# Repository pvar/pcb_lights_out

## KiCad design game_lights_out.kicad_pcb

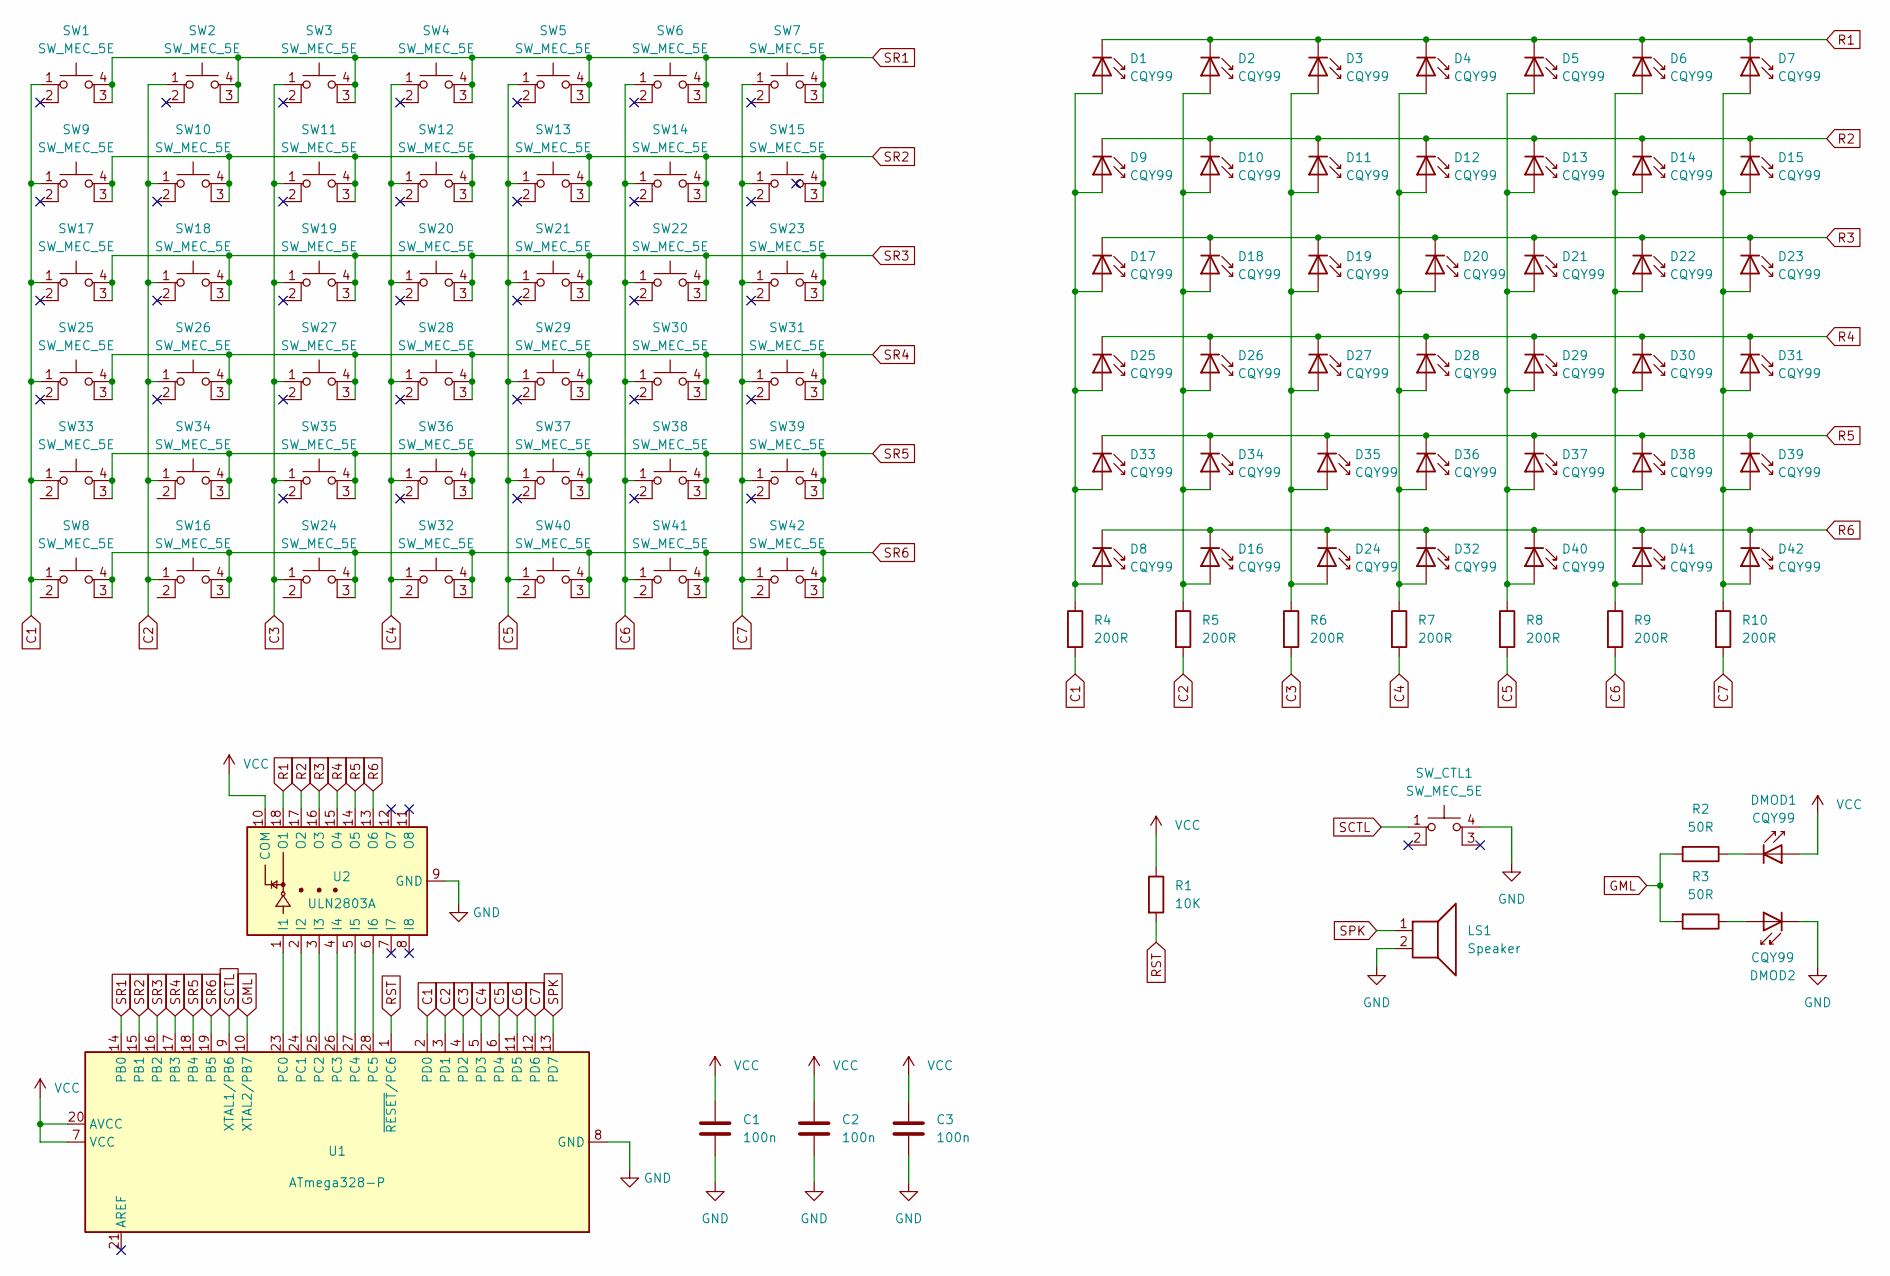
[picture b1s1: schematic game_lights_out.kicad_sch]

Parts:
C1, C2, C3: 100n; C_Rect_L4.6mm_W2.0mm_P2.50mm_MKS02_FKP02
D1, D2, D3, D4, D5, D6, D7, D8, D9, D10, D11, D12, D13, D14, D15, D16, D17, D18, D19, D20, D21, D22, D23, D24, D25, D26, D27, D28, D29, D30, D31, D32, D33, D34, D35, D36, D37, D38, D39, D40, D41, D42: CQY99; LED_D5.0mm
DMOD1, DMOD2: CQY99; LED_D1.8mm_W3.3mm_H2.4mm
LS1: Speaker; PinHeader_1x02_P2.54mm_Vertical
R1: 10K; R_Axial_DIN0207_L6.3mm_D2.5mm_P7.62mm_Horizontal
R2, R3: 50R; R_Axial_DIN0207_L6.3mm_D2.5mm_P7.62mm_Horizontal
R4, R5, R6, R7, R8, R9, R10: 200R; R_Axial_DIN0207_L6.3mm_D2.5mm_P7.62mm_Horizontal
SW1, SW2, SW3, SW4, SW5, SW6, SW7, SW8, SW9, SW10, SW11, SW12, SW13, SW14, SW15, SW16, SW17, SW18, SW19, SW20, SW21, SW22, SW23, SW24, SW25, SW26, SW27, SW28, SW29, SW30, SW31, SW32, SW33, SW34, SW35, SW36, SW37, SW38, SW39, SW40, SW41, SW42: SW_MEC_5E; SW_PUSH_6mm_H5mm
SW_CTL1: SW_MEC_5E; SW_PUSH_6mm_H5mm
U1: ATmega328-P; DIP-28_W7.62mm
U2: ULN2803A; DIP-18_W7.62mm

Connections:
C1: R4.2, SW1.1, SW8.1, SW9.1, SW17.1, SW25.1, SW33.1, U1.2 (PD0)
C2: R5.2, SW2.1, SW10.1, SW16.1, SW18.1, SW26.1, SW34.1, U1.3 (PD1)
C3: R6.2, SW3.1, SW11.1, SW19.1, SW24.1, SW27.1, SW35.1, U1.4 (PD2)
C4: R7.2, SW4.1, SW12.1, SW20.1, SW28.1, SW32.1, SW36.1, U1.5 (PD3)
C5: R8.2, SW5.1, SW13.1, SW21.1, SW29.1, SW37.1, SW40.1, U1.6 (PD4)
C6: R9.2, SW6.1, SW14.1, SW22.1, SW30.1, SW38.1, SW41.1, U1.11 (PD5)
C7: R10.2, SW7.1, SW15.1, SW23.1, SW31.1, SW39.1, SW42.1, U1.12 (PD6)
GML: R2.2, R3.2, U1.10 (XTAL2/PB7)
GND: C1.2, C2.2, C3.2, DMOD2.1 (K), LS1.2, SW_CTL1.4 (A), U1.8 (GND), U1.22 (GND), U2.9 (GND)
unnamed: D1.2 (A), D8.2 (A), D9.2 (A), D17.2 (A), D25.2 (A), D33.2 (A), R4.1
unnamed: D2.2 (A), D10.2 (A), D16.2 (A), D18.2 (A), D26.2 (A), D34.2 (A), R5.1
unnamed: D3.2 (A), D11.2 (A), D19.2 (A), D24.2 (A), D27.2 (A), D35.2 (A), R6.1
unnamed: D4.2 (A), D12.2 (A), D20.2 (A), D28.2 (A), D32.2 (A), D36.2 (A), R7.1
unnamed: D5.2 (A), D13.2 (A), D21.2 (A), D29.2 (A), D37.2 (A), D40.2 (A), R8.1
unnamed: D6.2 (A), D14.2 (A), D22.2 (A), D30.2 (A), D38.2 (A), D41.2 (A), R9.1
unnamed: D7.2 (A), D15.2 (A), D23.2 (A), D31.2 (A), D39.2 (A), D42.2 (A), R10.1
unnamed: DMOD1.1 (K), R2.1
unnamed: DMOD2.2 (A), R3.1
unnamed: U1.23 (PC0), U2.1 (I1)
unnamed: U1.24 (PC1), U2.2 (I2)
unnamed: U1.25 (PC2), U2.3 (I3)
unnamed: U1.26 (PC3), U2.4 (I4)
unnamed: U1.27 (PC4), U2.5 (I5)
unnamed: U1.28 (PC5), U2.6 (I6)
R1: D1.1 (K), D2.1 (K), D3.1 (K), D4.1 (K), D5.1 (K), D6.1 (K), D7.1 (K), U2.18 (O1)
R2: D9.1 (K), D10.1 (K), D11.1 (K), D12.1 (K), D13.1 (K), D14.1 (K), D15.1 (K), U2.17 (O2)
R3: D17.1 (K), D18.1 (K), D19.1 (K), D20.1 (K), D21.1 (K), D22.1 (K), D23.1 (K), U2.16 (O3)
R4: D25.1 (K), D26.1 (K), D27.1 (K), D28.1 (K), D29.1 (K), D30.1 (K), D31.1 (K), U2.15 (O4)
R5: D33.1 (K), D34.1 (K), D35.1 (K), D36.1 (K), D37.1 (K), D38.1 (K), D39.1 (K), U2.14 (O5)
R6: D8.1 (K), D16.1 (K), D24.1 (K), D32.1 (K), D40.1 (K), D41.1 (K), D42.1 (K), U2.13 (O6)
RST: R1.2, U1.1 (~RESET/PC6)
SCTL: SW_CTL1.1, U1.9 (XTAL1/PB6)
SPK: LS1.1, U1.13 (PD7)
SR1: SW1.3 (K), SW1.4 (A), SW2.3 (K), SW2.4 (A), SW3.3 (K), SW3.4 (A), SW4.3 (K), SW4.4 (A), SW5.3 (K), SW5.4 (A), SW6.3 (K), SW6.4 (A), SW7.3 (K), SW7.4 (A), U1.14 (PB0)
SR2: SW9.3 (K), SW9.4 (A), SW10.3 (K), SW10.4 (A), SW11.3 (K), SW11.4 (A), SW12.3 (K), SW12.4 (A), SW13.3 (K), SW13.4 (A), SW14.3 (K), SW14.4 (A), SW15.3 (K), SW15.4 (A), U1.15 (PB1)
SR3: SW17.3 (K), SW17.4 (A), SW18.3 (K), SW18.4 (A), SW19.3 (K), SW19.4 (A), SW20.3 (K), SW20.4 (A), SW21.3 (K), SW21.4 (A), SW22.3 (K), SW22.4 (A), SW23.3 (K), SW23.4 (A), U1.16 (PB2)
SR4: SW25.3 (K), SW25.4 (A), SW26.3 (K), SW26.4 (A), SW27.3 (K), SW27.4 (A), SW28.3 (K), SW28.4 (A), SW29.3 (K), SW29.4 (A), SW30.3 (K), SW30.4 (A), SW31.3 (K), SW31.4 (A), U1.17 (PB3)
SR5: SW33.3 (K), SW33.4 (A), SW34.3 (K), SW34.4 (A), SW35.3 (K), SW35.4 (A), SW36.3 (K), SW36.4 (A), SW37.3 (K), SW37.4 (A), SW38.3 (K), SW38.4 (A), SW39.3 (K), SW39.4 (A), U1.18 (PB4)
SR6: SW8.3 (K), SW8.4 (A), SW16.3 (K), SW16.4 (A), SW24.3 (K), SW24.4 (A), SW32.3 (K), SW32.4 (A), SW40.3 (K), SW40.4 (A), SW41.3 (K), SW41.4 (A), SW42.3 (K), SW42.4 (A), U1.19 (PB5)
VCC: C1.1, C2.1, C3.1, DMOD1.2 (A), R1.1, U1.7 (VCC), U1.20 (AVCC), U2.10 (COM)

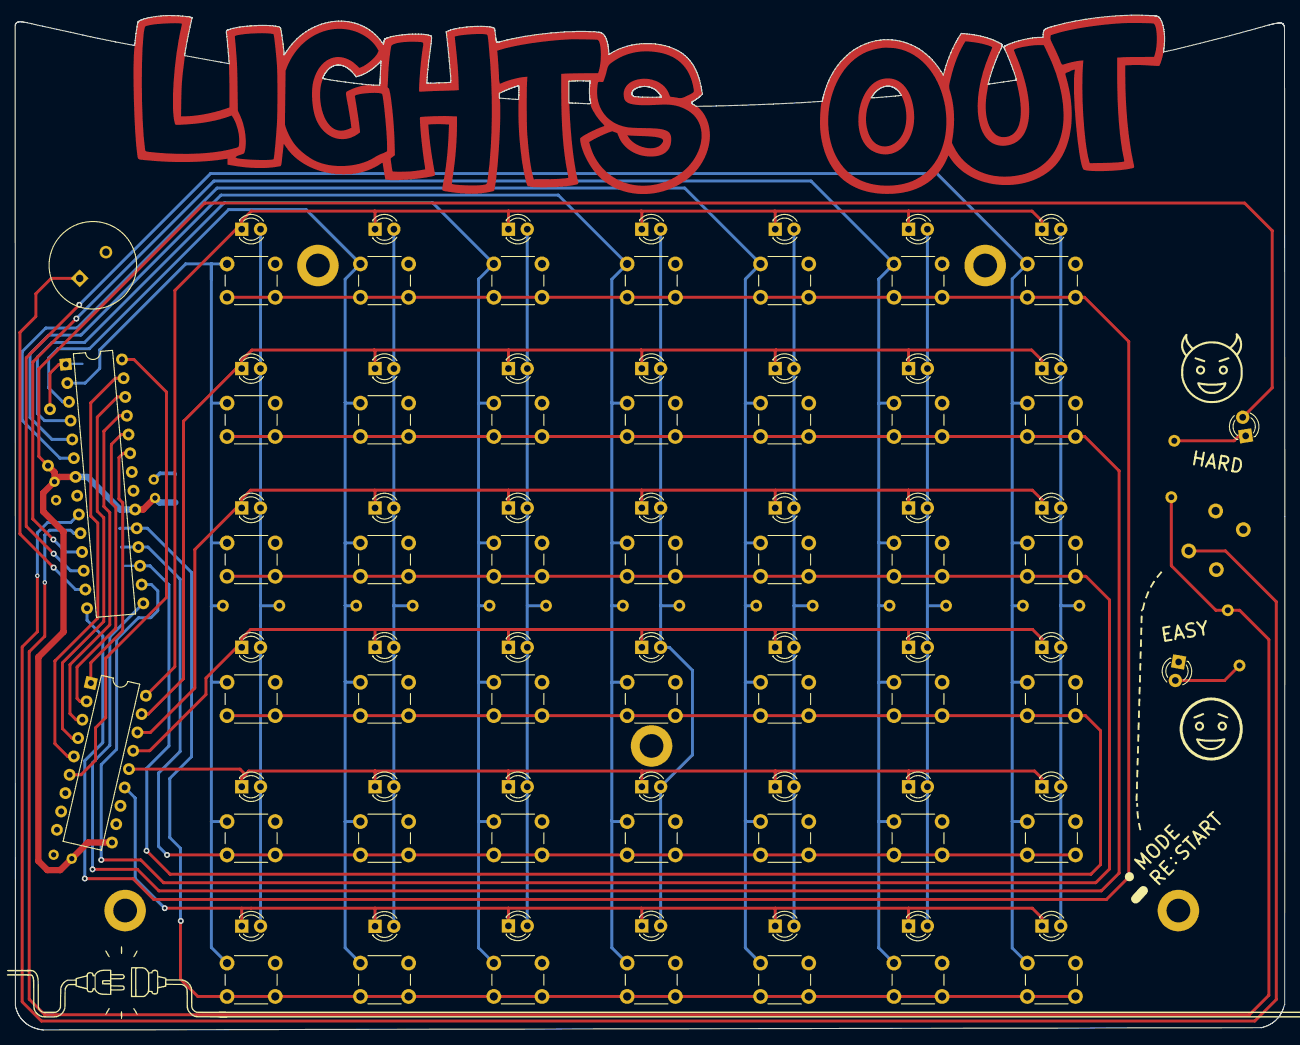
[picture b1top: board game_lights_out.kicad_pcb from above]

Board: 2 copper layers, 171.2 x 136.9 mm, 103 parts (0 on the bottom side), 40 nets.

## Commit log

2023-08-28 Final iteration
2023-08-28 Add signature on back silkscreen
2023-08-29 Added labels to programming pins and updated file format
2023-08-29 Removed reset pin resistor
2023-08-29 Added mounting holes
2023-08-29 Improved switch traces
2023-08-29 Fixed placement of holes and size of power vias
2023-09-01 Removed unnecessary shapes
2023-09-03 Added PCB render pictures
2023-09-03 Tweaked front side graphics
2023-09-03 Updated PCB pictures
2023-09-06 Added JLC order number placeholder
2023-09-15 Updated front side graphics
2023-09-16 Minor fixes in routing
2023-10-02 Added speaker
2023-10-05 Minor fixes on decorations
2023-10-10 Board clean up - Remove mounting holes - Remove component outlines - Remove matrix outline - Add SMD pads for power
2023-10-11 Increased contrast in title Removed white (silkscreen) fill from letters
2023-10-11 Removed JLCPCB batch-number placeholder
2023-10-12 Updated mounting holes
2023-10-27 Updated speaker size and placement
2023-10-27 Added order number placeholder (+ small fixes)
2023-11-07 Updated board pictures
2023-11-29 Minor tweaks
2024-01-23 Added reset pull up resitor
2024-01-25 Made text smaller
2024-02-06 Change mode/restart label to mode/start
2024-02-16 Major circuit redesign - matrix size is now 7 x 6 - resistors for matrix LEDs - game mode LEDs driven by single pin (cannot light simultaneously)
2024-02-22 WIP - major board redesign
2024-05-01 Major board redesign - rev2
2024-12-22 Solder pads for programming
